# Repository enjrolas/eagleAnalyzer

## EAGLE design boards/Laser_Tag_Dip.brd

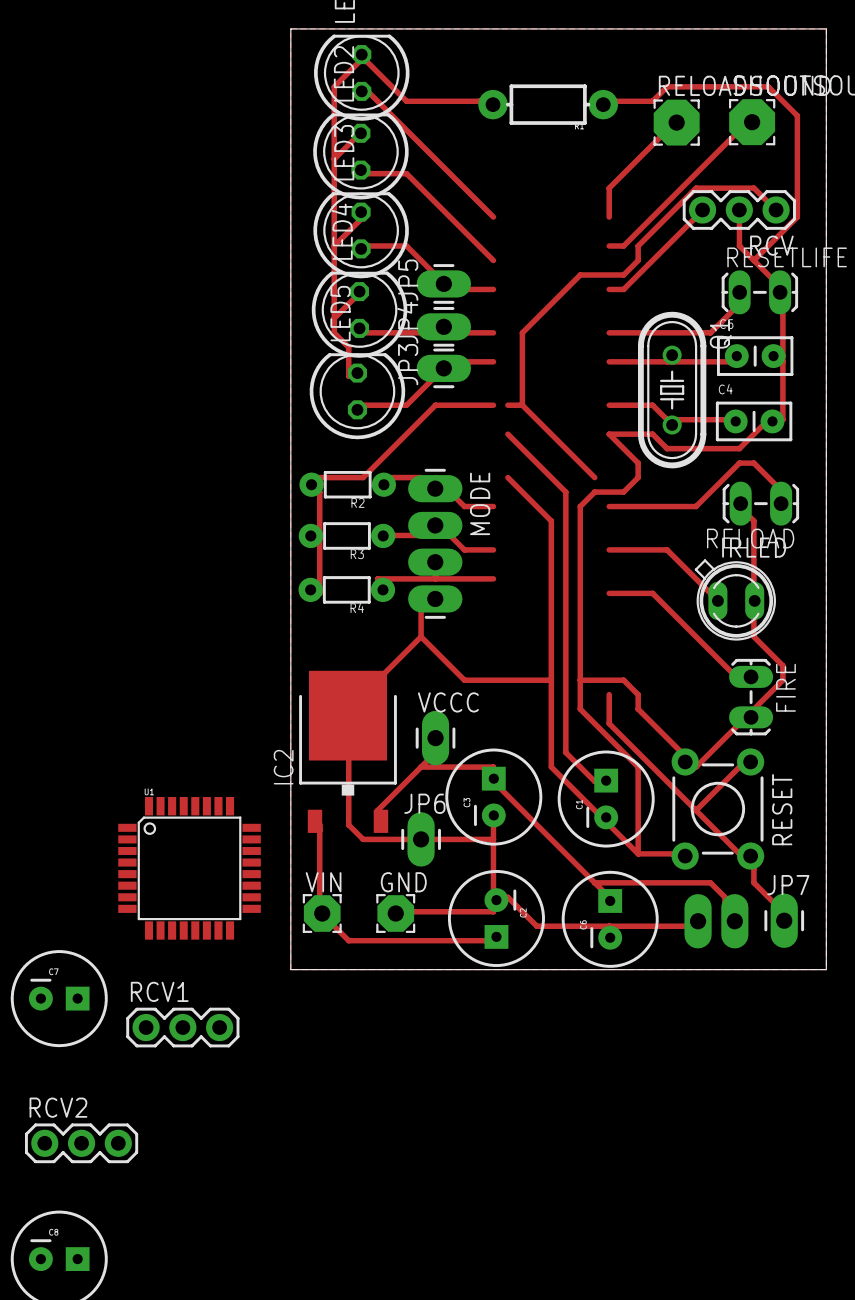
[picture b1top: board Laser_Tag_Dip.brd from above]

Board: 2 copper layers, 37.0 x 65.0 mm, 40 parts (0 on the bottom side), 23 nets.

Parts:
C1, C2, C3, C6, C7, C8: CPOL-RADIAL-100UF-25V
C4, C5: CAP-PTH-SMALLEZ
FIRE: 1X02_LOCK_LONGPADS
GND: GND PAD; 2,54/1,1
IC2: 7805DT; TO252
IRLED: SFH482
JP3: 13; 1X01_LONGPAD
JP4: 12; 1X01_LONGPAD
JP5: 11; 1X01_LONGPAD
JP6, JP7: M01PTH_LONGPAD; 1X01_LONGPAD
LED1, LED2, LED3, LED4, LED5: LED5MM
MODE: 1X04_LONGPADS
Q1: HC49/S
R1: AXIAL-0.3-KIT
R2, R3, R4: 1/6W-RES
RCV, RCV1, RCV2: IR RCVR; 1X03
RELOAD: 1X02_LOCK_LONGPADS
RELOADSOUND: RELOAD; 3,17/1,1
RESET: TACTILE-PTH
RESETLIFE: 1X02_LOCK_LONGPADS
SHOOTSOUND: SHOOT; 3,17/1,1
U1: ATMEGA168; TQFP32-08
VCCC: 5; 1X01_LONGPAD
VIN: Vin PAD; 2,54/1,1
VOUT: 1X02_LONGPADS

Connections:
CONNECT: FIRE.1, U1.32
GND: C1.2, C2.2, C3.2, C4.2, C5.2, C6.2, C7.2, C8.2, FIRE.2, GND.1, IC2.3, IRLED.K, JP6.1, MODE.4, R1.P$1, RCV.2, RCV1.2, RCV2.2, RELOAD.2, RESET.3, RESET.4, RESETLIFE.2, U1.3, U1.5, U1.21, VOUT.2
IR_RCV: RCV.3, RCV1.3, RCV2.3, U1.10
unnamed: C2.1, IC2.1, VIN.1
unnamed: C1.1, U1.20
unnamed: LED1.A, U1.13
unnamed: C5.1, Q1.1, U1.8
unnamed: LED2.A, U1.14
unnamed: C4.1, Q1.2, U1.7
unnamed: JP5.1, LED3.A, U1.15
unnamed: JP4.1, LED4.A, U1.16
unnamed: JP3.1, LED5.A, U1.17
unnamed: LED1.K, LED2.K, LED3.K, LED4.K, LED5.K, R1.P$2
unnamed: IRLED.A, U1.1
unnamed: RELOAD.1, U1.2
unnamed: RESETLIFE.1, U1.9
unnamed: MODE.1, R2.1, U1.23
unnamed: MODE.2, R3.1, U1.24
unnamed: MODE.3, R4.1, U1.25
RELOADSOUND: RELOADSOUND.1, U1.12
RESETWIRE: JP7.1, RESET.1, RESET.2, U1.29
SHOOTSOUND: SHOOTSOUND.1, U1.11
VCC: C3.1, C6.1, C7.1, C8.1, IC2.2, R2.2, R3.2, R4.2, RCV.1, RCV1.1, RCV2.1, U1.4, U1.6, U1.18, VCCC.1, VOUT.1

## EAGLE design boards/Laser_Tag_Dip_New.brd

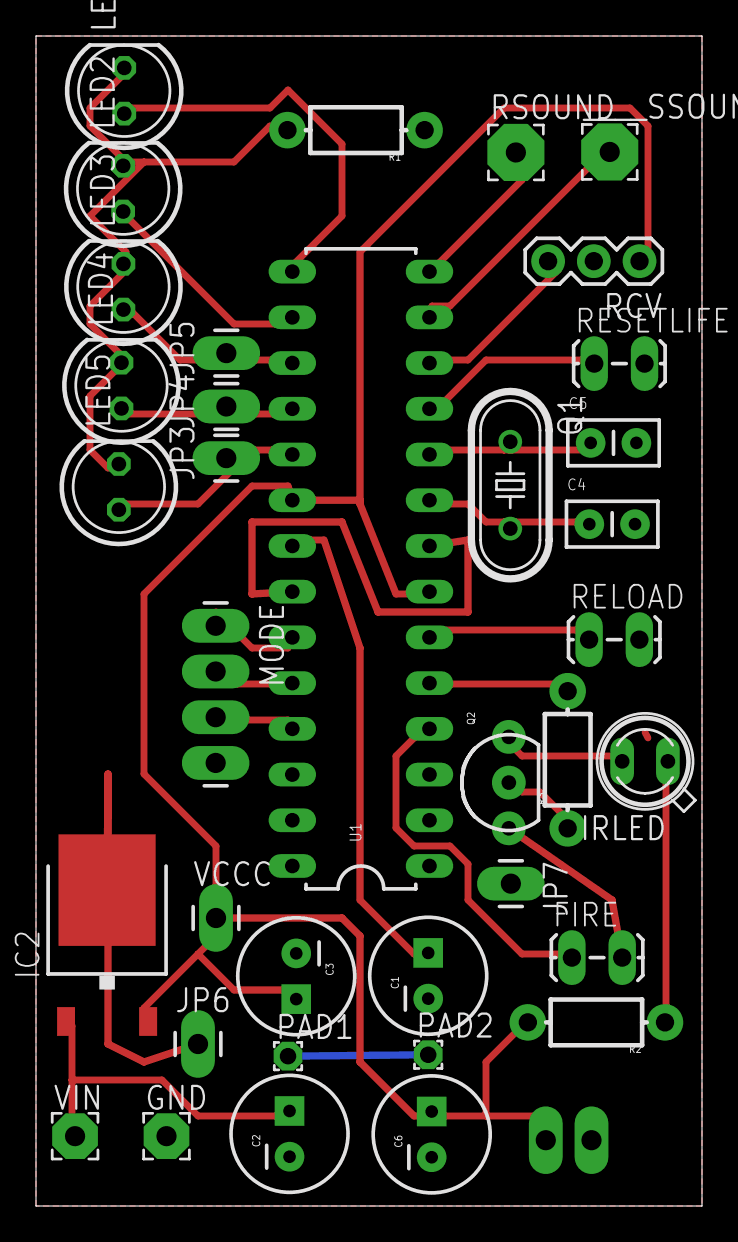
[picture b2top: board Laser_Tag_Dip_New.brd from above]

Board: 2 copper layers, 37.0 x 65.0 mm, 37 parts (0 on the bottom side), 25 nets.

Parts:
C1, C2, C3, C6: CPOL-RADIAL-100UF-25V
C4, C5: CAP-PTH-SMALLEZ
FIRE: 1X02_LOCK_LONGPADS
GND: GND PAD; 2,54/1,1
IC2: 7805DT; TO252
IRLED: SFH482
JP3: 13; 1X01_LONGPAD
JP4: 12; 1X01_LONGPAD
JP5: 11; 1X01_LONGPAD
JP6, JP7: M01PTH_LONGPAD; 1X01_LONGPAD
LED1, LED2, LED3, LED4, LED5: LED5MM
MODE: 1X04_LONGPADS
PAD1, PAD2: WIREPAD1,6/0,9; 1,6/0,9
Q1: HC49/S
Q2: TO-92-AMMO
R1, R2, R3: AXIAL-0.3-KIT
RCV: IR RCVR; 1X03
RELOAD: 1X02_LOCK_LONGPADS
RESETLIFE: 1X02_LOCK_LONGPADS
RSOUND: RELOAD; 3,17/1,1
U1: ATMEGA328P_PDIP; DIL28-3
VCCC: 5; 1X01_LONGPAD
VIN: Vin PAD; 2,54/1,1
VOUT: 1X02_LONGPADS
____SSOUND: SHOOT; 3,17/1,1

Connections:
CONNECT: FIRE.1, U1.4
GND: C1.2, C2.2, C3.2, C4.2, C5.2, C6.2, FIRE.2, GND.1, IC2.3, JP6.1, MODE.4, PAD1.1, PAD2.1, Q2.1, R1.P$1, RCV.2, RELOAD.2, RESETLIFE.2, U1.8, U1.22, VOUT.2
unnamed: C2.1, IC2.1, VIN.1
unnamed: C1.1, U1.21
unnamed: LED1.A, U1.15
unnamed: C5.1, Q1.1, U1.10
unnamed: LED2.A, U1.16
unnamed: C4.1, Q1.2, U1.9
unnamed: JP5.1, LED3.A, U1.17
unnamed: JP4.1, LED4.A, U1.18
unnamed: JP3.1, LED5.A, U1.19
unnamed: LED1.K, LED2.K, LED3.K, LED4.K, LED5.K, R1.P$2
unnamed: IRLED.K, Q2.3
unnamed: IRLED.A, R2.P$1
unnamed: RELOAD.1, U1.6
unnamed: RESETLIFE.1, U1.11
unnamed: RCV.3, U1.12
unnamed: Q2.2, R3.P$1
unnamed: MODE.1, U1.23
unnamed: MODE.2, U1.24
unnamed: MODE.3, U1.25
unnamed: R3.P$2, U1.5
RELOADSOUND: RSOUND.1, U1.14
SHOOTSOUND: U1.13, ____SSOUND.1
VCC: C3.1, C6.1, IC2.2, R2.P$2, RCV.1, U1.7, U1.20, VCCC.1, VOUT.1

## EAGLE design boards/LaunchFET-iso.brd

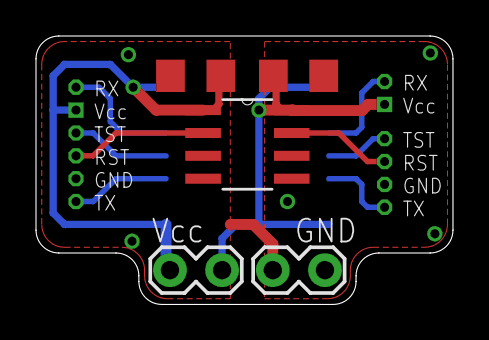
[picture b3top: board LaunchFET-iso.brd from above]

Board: 2 copper layers, 23.2 x 14.9 mm, 8 parts (1 on the bottom side), 12 nets.

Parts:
C1, C2: C1206
JP1, JP2: 1X02_LOCK
U2: ISO7231C_DW_16; DW16
U$2: ISO1540; D8
U$4: 6-PIN-ICSPEASY-MSP; EASYMSP-6PIN
U$5: 6-PIN-ICSPSAFE-MSP; SAFEMSP-6PIN

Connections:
GND_FET: C2.2, JP2.2, U2.2, U2.8, U$2.4, U$4.GND
GND_TARGET: C1.2, JP2.1, U2.9, U2.15, U$2.5, U$5.GND
RESET_FET: U$2.2, U$4.RST
RESET_TARGET: U$2.7, U$5.RST
RX_FET: U2.5, U$4.RX
RX_TARGET: U2.12, U$5.RX
TEST_FET: U2.4, U$4.TST
TEST_TARGET: U2.13, U$5.TST
TX_FET: U2.3, U$4.TX
TX_TARGET: U2.14, U$5.TX
VCC_FET: C2.1, JP1.1, U2.1, U2.7, U$2.1, U$4.VCC
VCC_TARGET: C1.1, JP1.2, U2.10, U2.16, U$2.8, U$5.VCC

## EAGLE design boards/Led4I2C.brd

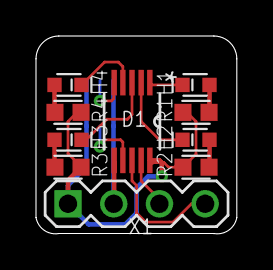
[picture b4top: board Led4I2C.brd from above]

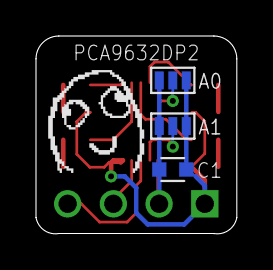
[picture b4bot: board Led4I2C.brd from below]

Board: 2 copper layers, 11.2 x 11.0 mm, 14 parts (4 on the bottom side), 14 nets.

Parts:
A0, A1: SJ-TRI; SJ-SMALL-TRI
C1: C0603
D1: PCA9632DP2,118; SOP50P490X110-10N
H1, H2, H3, H4: CHIP-LED0603
R1, R2, R3, R4: R0603
U$1: DAFUG
X1: PIIKKIRIMA-4

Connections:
+3V3: A0.1, A1.1, C1.1, D1.10, R1.2, R2.2, R3.2, R4.2, X1.1
A0: A0.3, D1.5
A1: A1.3, D1.7
GND: A0.2, A1.2, C1.2, D1.6, X1.2
LED0: D1.1, H1.C
LED1: D1.2, H2.C
LED2: D1.3, H3.C
LED3: D1.4, H4.C
unnamed: H1.A, R1.1
unnamed: H2.A, R2.1
unnamed: H3.A, R3.1
unnamed: H4.A, R4.1
SCL: D1.8, X1.4
SDA: D1.9, X1.3

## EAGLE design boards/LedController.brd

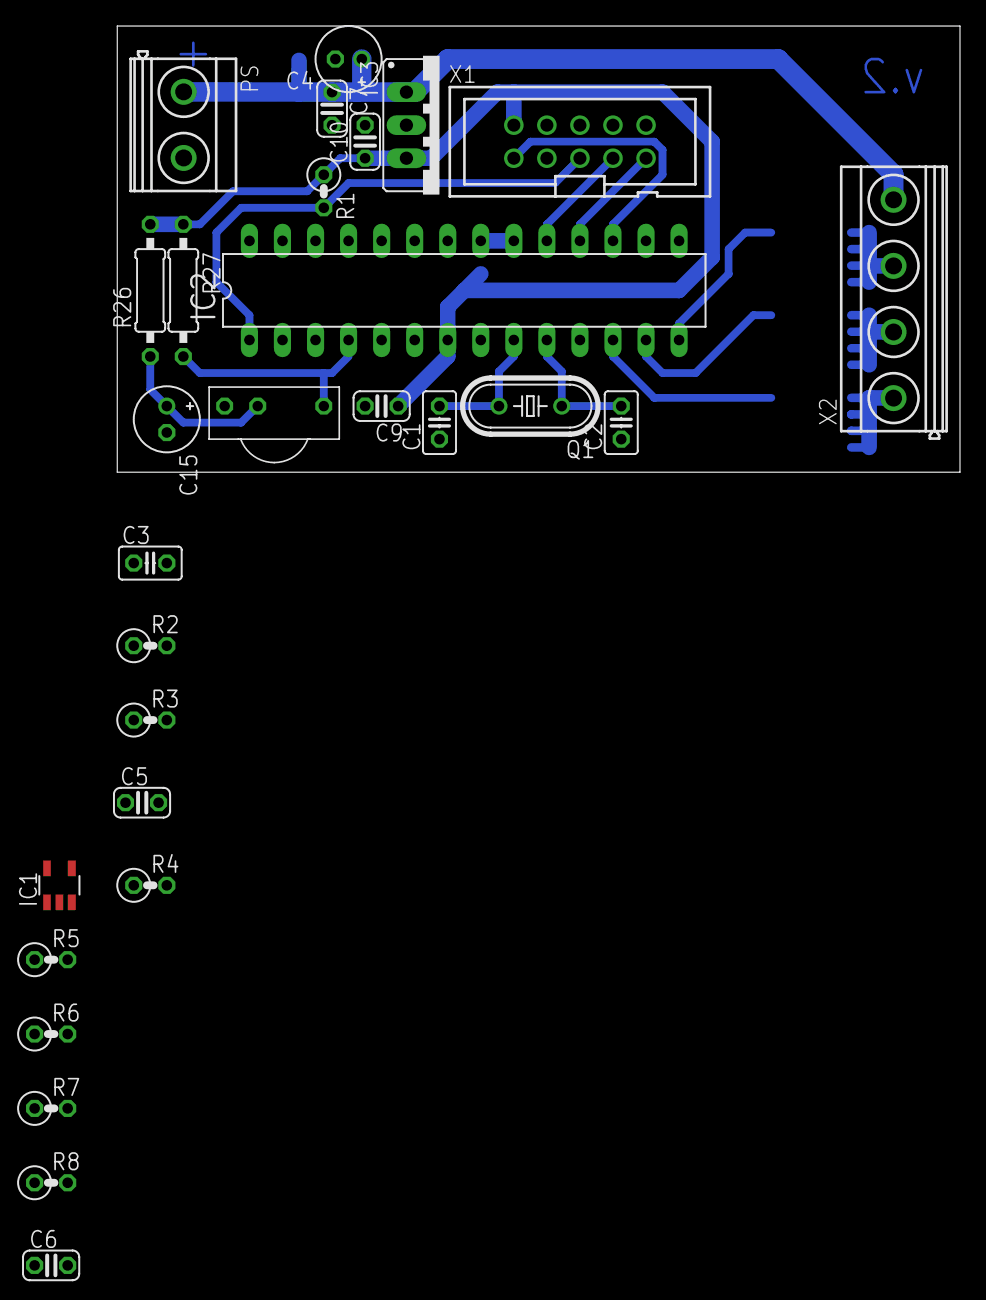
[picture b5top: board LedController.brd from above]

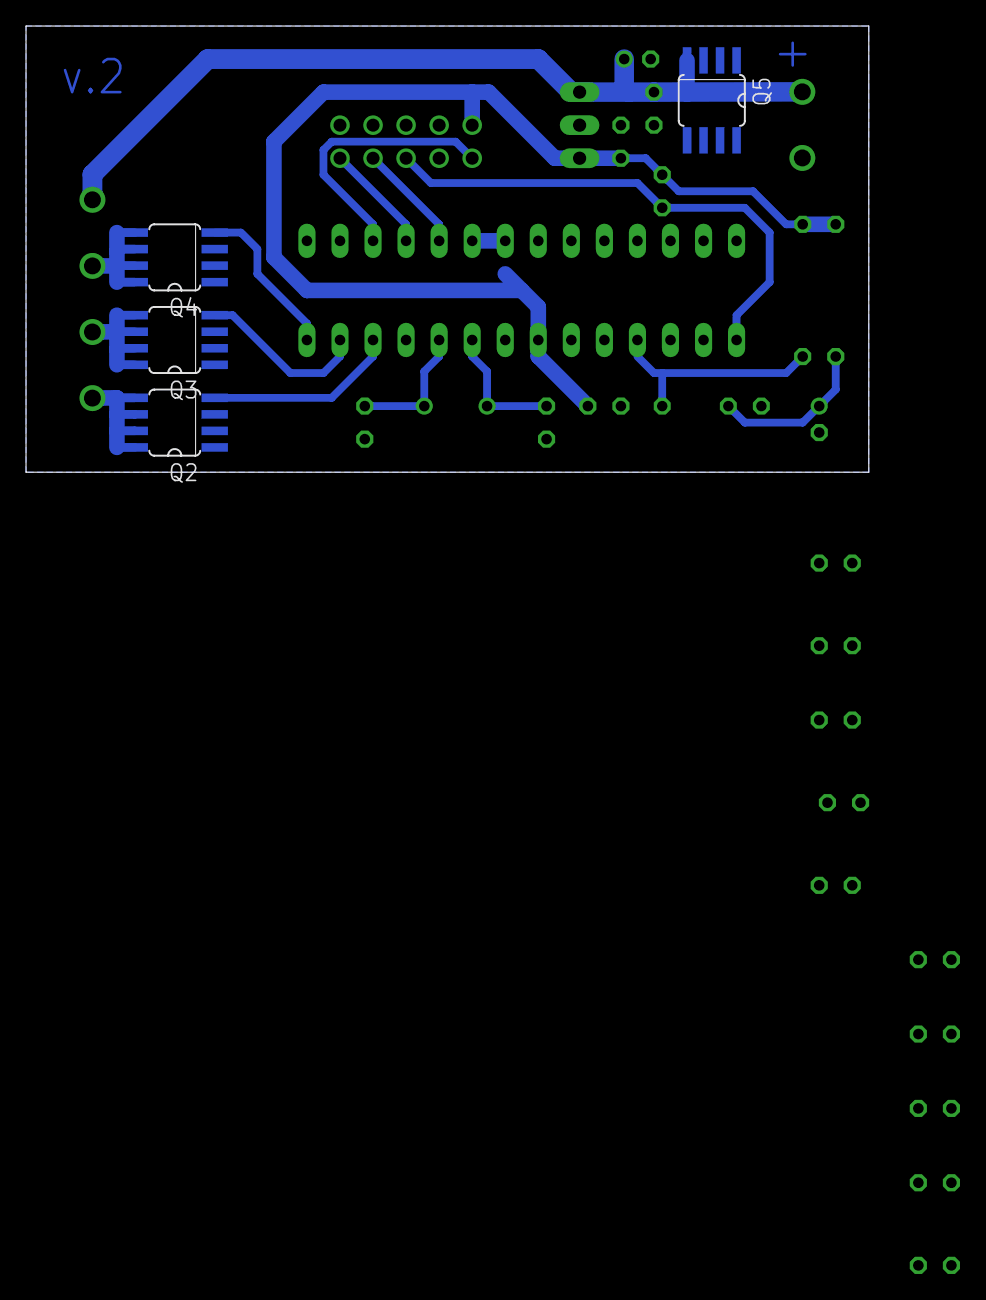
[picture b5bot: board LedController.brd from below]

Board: 2 copper layers, 64.8 x 34.3 mm, 32 parts (4 on the bottom side), 25 nets.

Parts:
C1, C2: 22pF; C025-025X050
C3: 100nF; C025-025X050
C4: 100uF; E2-5
C5: 1uF; C025-024X044
C6: 4n7; C025-024X044
C7, C9, C10: 100nF; C025-024X044
C15: 4.7uF; E2-5
IC1: MCP601R; SOT23-5
IC2: MEGA8-P; DIL28-3
IC3: 7805; 78XXS
PS: MKDSN1,5/2-5,08
Q1: 16MHz; HC49/S
Q2, Q3, Q4, Q5: FDS8884; SO08
R1, R5, R6, R7: 10k; 0207/2V
R2: 100; 0207/2V
R3, R4: 1k; 0207/2V
R8: 12k; 0207/2V
R26: 100R; 0207/10
R27: 10k; 0207/10
TSOP: TSOP
X1: 2510-; PAK100/2500-10
X2: MKDSN1,5/4-5,08

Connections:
+5V: C9.1, C10.1, IC1.2, IC2.7, IC3.OUT, R1.1, R2.2, R3.2, R5.1, R26.2, R27.1, X1.2
+12V: C4.+, C7.1, IC3.IN, PS.1, Q5.4, X2.4
ADC: C6.2, IC2.23, R8.2
GND: C1.1, C2.1, C3.2, C4.-, C6.1, C7.2, C9.2, C10.2, C15.-, IC1.5, IC2.8, IC2.22, IC3.GND, Q2.1, Q2.2, Q2.3, Q3.1, Q3.2, Q3.3, Q4.1, Q4.2, Q4.3, Q5.1, Q5.2, Q5.3, R6.2, TSOP.GND, X1.4, X1.6, X1.8, X1.10
IR: IC2.4, R27.2, TSOP.VO
ISP_CLK: IC2.19, X1.7
ISP_MISO: IC2.18, X1.9
ISP_MOSI: IC2.17, X1.1
ISP_RESET: IC2.1, R1.2, X1.5
unnamed: C5.1, R3.1
unnamed: C1.2, IC2.9, Q1.2
unnamed: C2.2, IC2.10, Q1.1
unnamed: Q2.5, Q2.6, Q2.7, Q2.8, X2.1
unnamed: Q3.5, Q3.6, Q3.7, Q3.8, X2.2
unnamed: Q4.5, Q4.6, Q4.7, Q4.8, X2.3
unnamed: C3.1, IC2.20, IC2.21, R2.1
unnamed: PS.2, Q5.5, Q5.6, Q5.7, Q5.8
unnamed: C5.2, R4.2, R7.1
unnamed: IC1.4, R4.1
unnamed: IC1.3, R5.2, R6.1
unnamed: IC1.1, R7.2, R8.1
unnamed: C15.+, R26.1, TSOP.VS
PWM_B: IC2.14, Q4.4
PWM_G: IC2.13, Q3.4
PWM_R: IC2.12, Q2.4

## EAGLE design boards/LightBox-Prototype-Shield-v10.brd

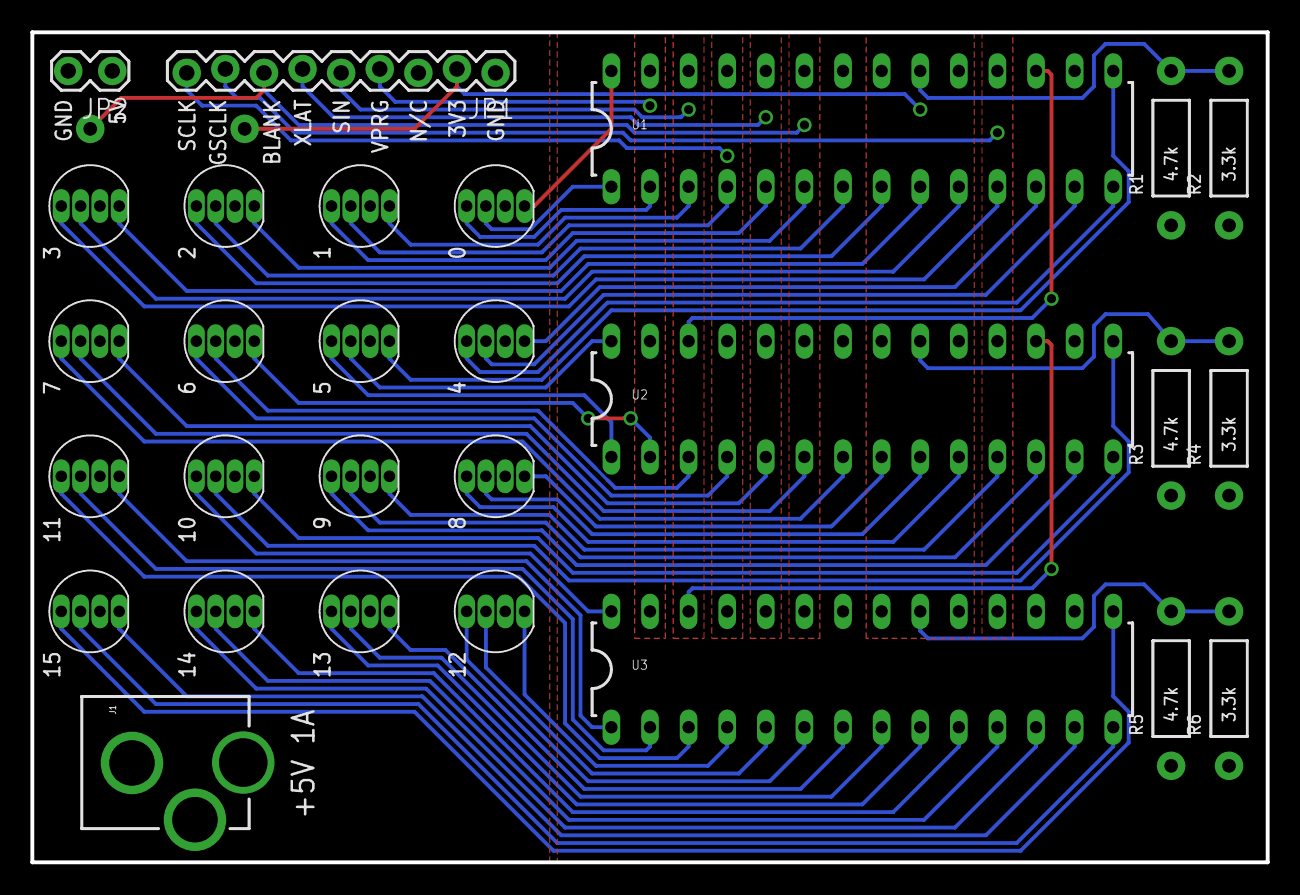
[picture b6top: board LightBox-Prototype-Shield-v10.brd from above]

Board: 2 copper layers, 81.3 x 54.6 mm, 29 parts (1 on the bottom side), 62 nets.

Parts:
D1, D2, D3, D4, D5, D6, D7, D8, D9, D10, D11, D12, D13, D14, D15, D16: LED-RGB-CA-THRUDIFFUSE; LED-RGB-THRU
J1: POWER_JACKPTH_LOCK; POWER_JACK_PTH_LOCK
JP1: M09LOCK; 1X09_LOCK
JP2: 1X02_LOCK
R1, R3, R5: 4.7k; AXIAL-0.4
R2, R4, R6: 3.3k; AXIAL-0.4
R7: 10k; AXIAL-0.4
U1, U2, U3: TLC5940-NT; DIL28-3

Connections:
+3V3: JP1.2, R7.P$2, U1.19, U1.21, U2.19, U2.21, U3.19, U3.21
GND: J1.GND, J1.GNDBREAK, JP1.1, JP2.2, R1.P$1, R2.P$1, R3.P$1, R4.P$1, R5.P$1, R6.P$1, U1.22, U2.22, U3.22
unnamed: D1.1, U1.28
unnamed: D1.3, U1.1
unnamed: D1.4, U1.2
unnamed: D2.1, U1.3
unnamed: D2.3, U1.4
unnamed: D2.4, U1.5
unnamed: D3.1, U1.6
unnamed: D3.3, U1.7
unnamed: D3.4, U1.8
unnamed: D4.1, U1.9
unnamed: D4.3, U1.10
unnamed: D4.4, U1.11
unnamed: D5.1, U1.12
unnamed: D5.3, U1.13
unnamed: D5.4, U1.14
unnamed: D6.1, U1.15
unnamed: D6.3, U2.28
unnamed: D6.4, U2.1
unnamed: D7.1, U2.2
unnamed: D7.3, U2.3
unnamed: D7.4, U2.4
unnamed: D8.1, U2.5
unnamed: D8.3, U2.6
unnamed: D8.4, U2.7
unnamed: D9.1, U2.8
unnamed: D9.3, U2.9
unnamed: D9.4, U2.10
unnamed: D10.1, U2.11
unnamed: D10.3, U2.12
unnamed: D11.3, U2.15
unnamed: D10.4, U2.13
unnamed: D11.1, U2.14
unnamed: D11.4, U3.28
unnamed: D12.1, U3.1
unnamed: D12.3, U3.2
unnamed: D12.4, U3.3
unnamed: D13.1, U3.4
unnamed: D13.3, U3.5
unnamed: D13.4, U3.6
unnamed: D14.1, U3.7
unnamed: D14.3, U3.8
unnamed: D14.4, U3.9
unnamed: D15.1, U3.10
unnamed: D15.3, U3.11
unnamed: D15.4, U3.12
unnamed: D16.1, U3.13
unnamed: D16.3, U3.14
unnamed: D16.4, U3.15
unnamed: R1.P$2, R2.P$2, U1.20
unnamed: R3.P$2, R4.P$2, U2.20
unnamed: R5.P$2, R6.P$2, U3.20
unnamed: U1.17, U2.26
unnamed: U2.17, U3.26
PIN1: JP1.9, U1.25, U2.25, U3.25
PIN2: JP1.8, U1.18, U2.18, U3.18
PIN5: JP1.7, R7.P$1, U1.23, U2.23, U3.23
PIN7: JP1.6, U1.24, U2.24, U3.24
PIN8: JP1.5, U1.26
PIN9: JP1.4, U1.27, U2.27, U3.27
VCC: D1.2, D2.2, D3.2, D4.2, D5.2, D6.2, D7.2, D8.2, D9.2, D10.2, D11.2, D12.2, D13.2, D14.2, D15.2, D16.2, J1.PWR, JP2.1

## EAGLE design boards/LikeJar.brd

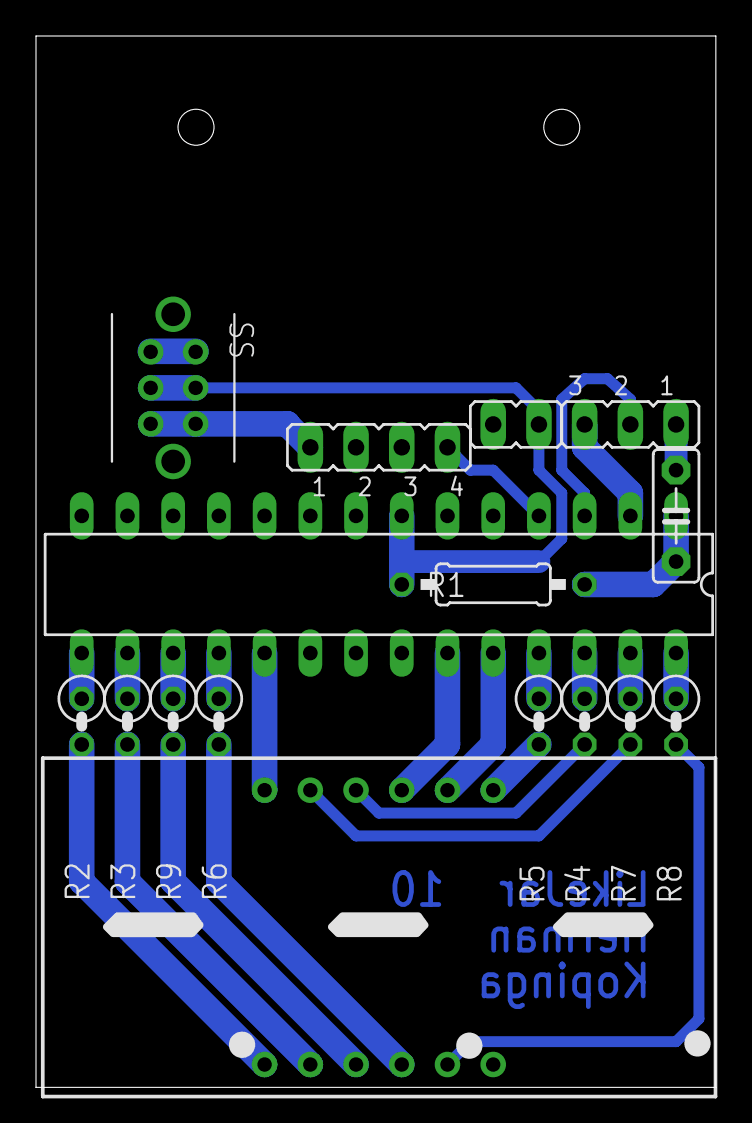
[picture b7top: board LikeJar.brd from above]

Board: 2 copper layers, 37.8 x 58.4 mm, 16 parts (0 on the bottom side), 27 nets.

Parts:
ASDF1: SS
C3: 0,1 uF; C5B2.5
IC1: MEGA8-P; DIL28-3
JP1: JP4
JP5: JP2
JP6: JP1
LED4: BA56-12SRWA; BX56-12
R1: 10 kΩ; 0207/10
R2, R3, R4, R5, R6, R7, R8, R9: 120 Ω; 0207/2V

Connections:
GND: ASDF1.P$1, ASDF1.P$2, IC1.8, IC1.22, JP1.2, JP1.3, JP6.2
unnamed: ASDF1.IN1, ASDF1.IN2, IC1.7, JP6.1, R1.1
unnamed: C3.2, IC1.1, R1.2
unnamed: LED4.7, R5.2
unnamed: LED4.11, R7.2
unnamed: LED4.4, R6.2
unnamed: LED4.2, R3.2
unnamed: LED4.1, R2.2
unnamed: LED4.10, R4.2
unnamed: LED4.5, R8.2
unnamed: LED4.3, R9.2
unnamed: C3.1, JP5.1
unnamed: IC1.26, R4.1
unnamed: IC1.4, JP1.4
unnamed: IC1.23, LED4.9
unnamed: IC1.24, LED4.8
unnamed: IC1.17, R9.1
unnamed: IC1.28, R8.1
unnamed: IC1.25, R5.1
unnamed: IC1.15, R2.1
unnamed: IC1.16, R3.1
unnamed: IC1.27, R7.1
unnamed: IC1.19, LED4.12
unnamed: IC1.18, R6.1
unnamed: IC1.3, JP5.2
unnamed: IC1.2, JP5.3
VCC: ASDF1.OUT1B, ASDF1.OUT2B, JP1.1

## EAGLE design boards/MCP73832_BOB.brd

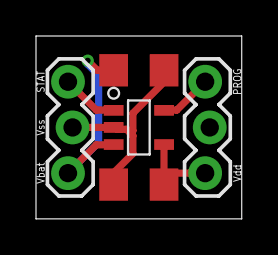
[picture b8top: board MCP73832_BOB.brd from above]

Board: 2 copper layers, 11.4 x 10.2 mm, 5 parts (0 on the bottom side), 5 nets.

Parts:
C1, C2: 1206
JP1, JP2: 1X03_LOCK
U$2: MCP73832; SOT-23(OT)5_LEAD

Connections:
GND: C1.2, C2.2, JP1.2, U$2.2
unnamed: C1.1, JP1.1, U$2.3
unnamed: JP1.3, U$2.1
unnamed: JP2.3, U$2.5
unnamed: C2.1, JP2.1, U$2.4

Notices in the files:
parts and their libraries:
SparkFun-Capacitors: Licensing: CC v3.0 Share-Alike You are welcome to use this library for commercial purposes.
